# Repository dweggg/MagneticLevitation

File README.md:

# MagneticLevitation
My take on one of those active magnetic levitation projects.

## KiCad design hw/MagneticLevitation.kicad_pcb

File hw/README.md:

# Issues

[ ] -> open
[X] -> found

[X] 1. U1 (3V3 buck) was ordered with JLC PN C61063 (XLSEMI XL1509-5.0E1), which is 5V output, and it should've been C74193 (XLSEMI XL1509-3.3E1). Regardless, it outputs ~4.38V out with ~5.1V in. MCU can be flashed and all aber das ist nicht richtig.

[X] 2. U2 and L2 were removed bc that caused L2 to overheat, something might be wrong with gate drivers (chips or bootstrap). No power for now.

[X] 3. NTC reads 0V, so either pin is bad/misconfigured, or C31 is shorted or something (~0Ohm between TP13 and GND)

[X] 4. Some boards have the inductor rotated 90deg!! That would make the boost not work at all

[X] 5. Vbus sag with pulsed current in a coil around the board. I don't think it's a good idea to have inductors wound in the same axis as the coil we're trying to control, but is there any alternative?

---

Finding: my dumbass didn't configure short circuit rules and there's a group of vias to GND short circuiting the following nets to GND:

- SWA
- SWB
- Gate AH/BH (before gate resistor)
- Vboot_A/B (top side of bootstrap capacitor)
- tempMeas

These are all in the bottom inner layer so it can't be seen on the PCB itself. Fix for now could be a nasty cut traces+magnet wire to destination but that'll require some proper tools... But maybe I'll skip that and probably order again when firmware is ~80% there.

So that explains issues #2 and #3: L2 was overheating bc it's rated at 100mA, and when the boost is disabled, the inductor is getting the 3.3V (well, 4.38V) to the gate driver supply, and since Vboot is shorted to GND, it goes trough R16/R17 to D6/D7 to GND... That's also why the power output (SWA/SWB) was shorted to ground, initially I thought it was some sort of gate driver protection magically turning on the low side switch but no lol.

I think I might have added those two via groups to lower switching loop inductance just before producing outputs and didn't run DRC... That was not a very expensive mistake but a very stupid one for sure. We can use rev1 for improving some other minor things found only after ordering.

---

# Changes to be made
[ ] -> Pending
[S] -> Schematic only
[P] -> Partially done
[X] -> Complete

- [X] 1. Remove violating via groups
- [X] 2. Swap LCSC PN for U1 (XLSEMI XL1509-3.3E1) -> see change #23
- [X] 3. Review LED resistor values: by lowering VCC to the correct 3.3V all LEDs should have a more reasonable brightness, increased to 220R anyways.
- [X] 4. Add external fixed voltage reference, maybe even replacing iRef divider? -> adjusting acq window seems to fix current. Pending tests with real current, but i think it's not needed now that we have a LDO (change #23)
- [X] 5. Add EEPROM?: I don't think we'd need it, and if we really needed it there's a ch32 eeprom emulation using flash, but will give it some thought. So far I don't think we need it, we have plenty of spare flash still with firmware close to 80% of the features, so crossing this one off.
- [X] 6. Review RST button behavior, or think of a way to hw reset the MCU, without firmware -> not necessary, but if needed current design could be made work like that if we flashed with a debugger and not with the bootloader
- [X] 7. Disconnect U2 (MT3608) output without EN pin, PMOS maybe -> not needed, drivers have UVLO at 5.5V
- [X] 8. Remove JLCJLCJLCJLC
- [X] 9. Move power supply section a bit down and leave more clearance with board edge
- [X] 10. Move debug/UART connectors and RST button, also turn them DNP
- [X] 11. Improve bootstrap layout? Works just fine even with the ugly rework, not needed.
- [X] 12. Replace expensive capacitors with something cheaper available as basic JLCPCBA: So far replaced all 22uF with 10uF. Pending proper review with BOM. removed yet another bom line! Was cheap enough already i think.
- [X] 13. Find cuter output connector? Maybe even SMD so back side stays clean -> found a cute but expensive wago. worth it imo
- [X] 14. Review Rgate, since at 12V V_GS, I_G_pk = 12V/10R = 1.2A which is bigger than XJNG2103 1A -> increased to 15R
- [X] 15. Try to reduce electrolytic cap height? If we have XY space we can have half capacitance, half height but x2 parts -> reduced to 5.6mm, same as connector, without decreasing C or increasing diameter. Doesnt make sense to go lower unless connector goes lower, which is not happening
- [X] 16. R16/R17 should be a bit bigger if they need to be hand replaced -> part of bootstrap, same thing, it works
- [X] 17. Testpoints for gates!!! Even if they're difficult to place
- [X] 18. Add revision number in sch and pcb
- [X] 19. Automatic bootloader entry with a MOSFET or similar instead of button (or parallel to button) -> meh not worth it. The flashing experience through bootloader is not that bad. TI is 200x worse even with a fancy jtag probe
- [X] 20. Add potentiometer for setpoint percentage of power
- [X] 21. Add sillkscreen for board ID
- [X] 22. Fix for issue #4 -> added FT Rotation Offset field and set to 0, but investigation is pending. Handled with an assembly remark in prod.
- [X] 23. Fix for issue #5: Replaced 3V3 buck with LDO which removes change #2. I was scared of the inductor saturating and maybe doing something funny with the analog rail. Playing safe even though it clearly works somehow in the current version.

---

# To be verified w current rev before ordering:

[ ] -> Pending
[P] -> Partially done
[X] -> Complete

- [X] 1. Current measurement: At first it looked fine but I noticed it's a little bit asymmetrical with positive and negative setpoints. not a problem, since the important thing is that the controller is fast, not accurate. But maybe can be fine tuned. I think I'm closing it since it doesnt make much of a difference to have 200mA error when the position controller is jerking the current setpoint between -5A and 5A
- [X] 2. Magnetic field measurement: idk lol. It seems proportional to current without magnet (good!), and sort of checks out with what's expected of magnet. Other than that, lol idk. I guess it's fine. the control loop is more important than the accuracy of this sensor
- [X] 3. USB PD + Voltage measurement: ahh I'll have to be smart about how to test this, since my laptop's usb probably can't do very much. we have LEDs tho, that can be useful -> Firmware was able to request 20V from my laptop charger, I think we're good. but having debug + USBPD would be goated. My idea is to have the current comms stack routed to uart and using it instead of the usb port.
- [X] 4. Temperature measurement: cut traces+jump for avoiding issue #3, then thermal cam to verify I guess. So far the measurement seems reasonable with reality, but to be checked against a better measurement. I used a hairdryer to warm the board and i think it's accurate, my cooking skills allow me to distinguish temperatures above and below 60degC so i believe it's fine. its not that critical, even 10deg error would probably be ok. but i think we're at 2deg error, guesstimating. coil gets quite hot too, could we even measure that?
- [P] 5. Gate driver: cut traces+jump (nasty, 6 nets), then program PWM open loop and use scope, verify bootstrap against SPICE -> after i reworked the board i didnt give a fuck and tested power directly without checking gate driver, i have no waveforms but the board is able to control current pretty well. 5W no problem! next up is 100W from USB PD.
- [P] 6. Power: make em MOSFETs warm. Yeah so 5W so far. More to come after USB PD+comms

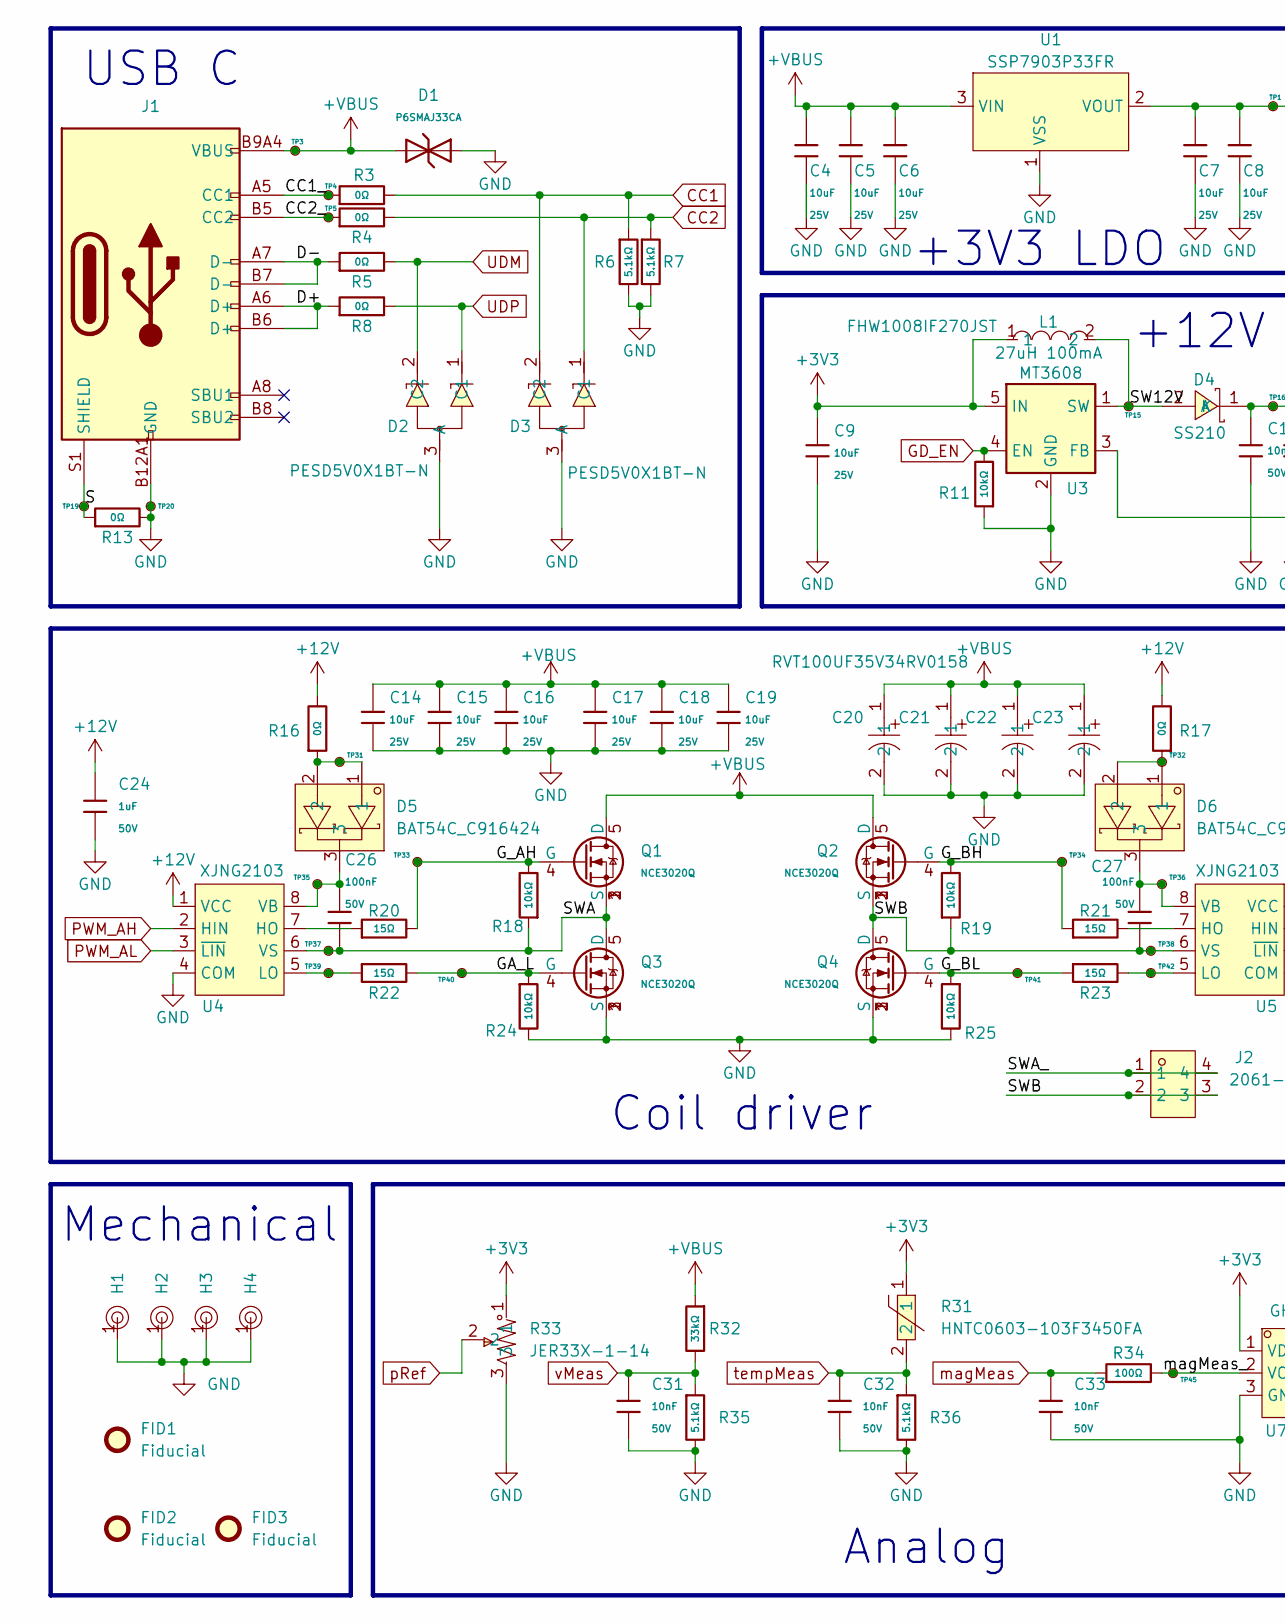
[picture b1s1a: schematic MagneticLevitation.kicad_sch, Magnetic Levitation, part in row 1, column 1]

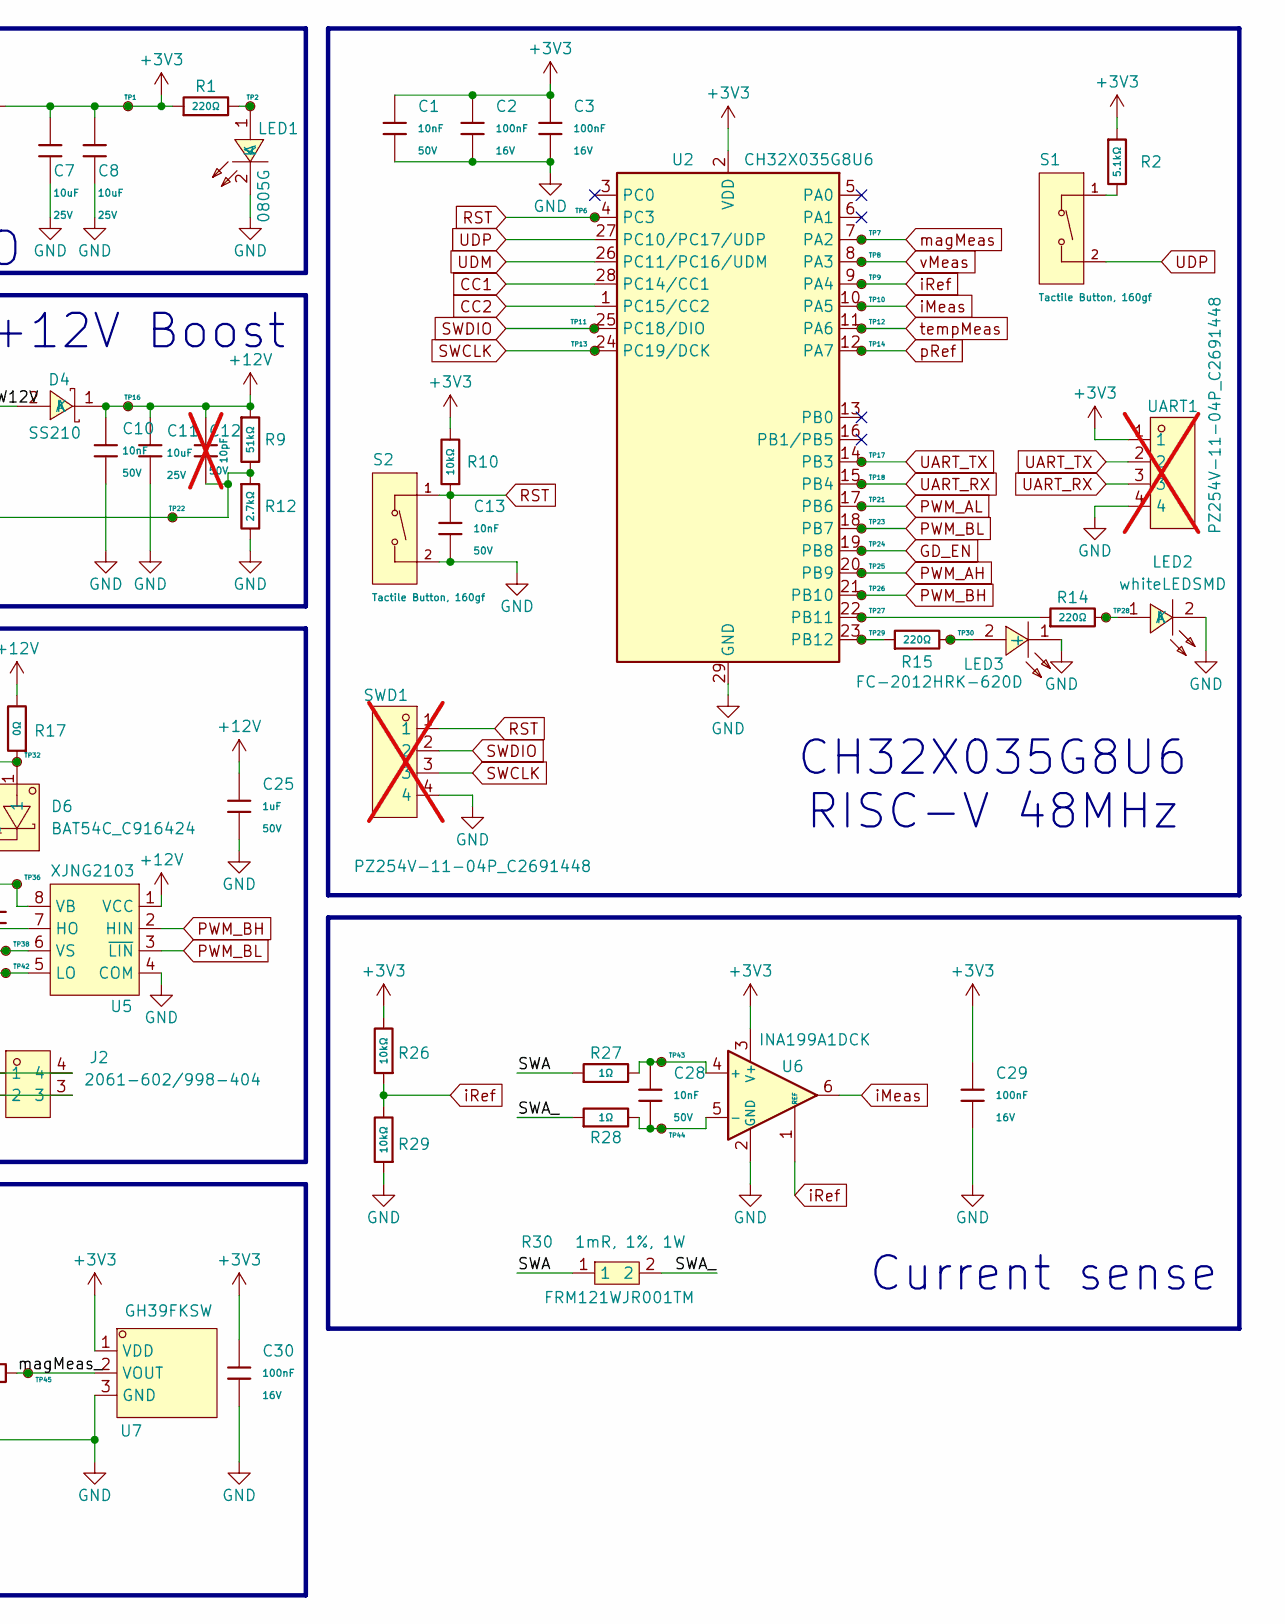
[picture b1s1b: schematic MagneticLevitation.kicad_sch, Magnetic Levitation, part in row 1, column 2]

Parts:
C1, C10, C28: 10nF; C_0402; Voltage Rated 50V; Tolerance ±10%; Part CL05B103KB5NNNC; LCSC C15195
C2, C3, C29, C30: 100nF; C_0402; Voltage Rated 16V; Tolerance ±10%; Part CL05B104KO5NNNC; LCSC C1525
C4, C5, C6, C7, C8, C9, C11, C14, C15, C16, C17, C18, C19: 10uF; C_0805; Voltage Rated 25V; Tolerance ±10%; Part CL21A106KAYNNNE; LCSC C15850
C12: 10pF; C_0603; Voltage Rated 50V; Tolerance ±5%; Part CL10C100JB8NNNC; LCSC C1634; not fitted
C13, C31, C32, C33: 10nF; C_0603; Voltage Rated 50V; Tolerance ±10%; Part 0603B103K500NT; LCSC C57112
C20, C21, C22, C23: RVT100UF35V34RV0158; CAP-SMD_BD6.3-L6.6-W6.6-LS7.2-FD_3; MPN VT100UF35V34RV0158; LCSC Part C2887272
C24, C25: 1uF; C_0805; Voltage Rated 50V; Tolerance ±10%; Part CL21B105KBFNNNE; LCSC C28323
C26, C27: 100nF; C_0603; Voltage Rated 50V; Tolerance ±10%; Part CC0603KRX7R9BB104; LCSC C14663
D1: P6SMAJ33CA; D_DO-214AC(SMA); Breakdown Voltage 36.7V; Part P6SMAJ33CA; LCSC C3019524
D2, D3: PESD5V0X1BT-N; SOT-23-3_L2.9-W1.3-P1.90-LS2.4-BR; MPN PESD5V0X1BT-N; LCSC Part C920303
D4: SS210; SMA_L4.3-W2.6-LS5.2-RD; MPN SS210; LCSC Part C14996
D5, D6: BAT54C_C916424; SOT-23-3_L2.9-W1.3-P1.90-LS2.4-BR; MPN BAT54C; LCSC Part C916424
FID1, FID2, FID3: Fiducial; Fiducial_0.5mm_Mask1.5mm
H1, H2, H3, H4: Hole, 3mm
J1: Connector, USB-TYPE-C-16P; TYPE-C-SMD_HX-TYPE-C-16PIN; LCSC C2927039
J2: 2061-602/998-404; CONN-SMD_2061-602-998-404; MPN 2061-602/998-404; LCSC Part C2765058
L1: 27uH 100mA; IND-SMD_L2.9-W2.8; MPN FHW1008IF270JST; LCSC Part C394070
LED1: 0805G; LED0805-R-RD; MPN KT-0805G; LCSC Part C2297
LED2: whiteLEDSMD; LED0805-R-RD; MPN KT-0805W; LCSC Part C34499
LED3: FC-2012HRK-620D; LED0805-RD; MPN NCD0805R1; LCSC Part C84256
Q1, Q2, Q3, Q4: NCE3020Q; NCE3020Q_DFN3.3x3.3-8L; Part NCE3020Q; LCSC C918240
R1, R14, R15: 220Ω; R_0603; Overload Voltage (Max) 75V; Tolerance ±1%; Part 0603WAF2200T5E; LCSC C22962
R2, R35, R36: 5.1kΩ; R_0603; Overload Voltage (Max) 75V; Tolerance ±1%; Part 0603WAF5101T5E; LCSC C23186
R3, R4, R5, R8, R13, R16, R17: 0Ω; R_0402; Overload Voltage (Max) 50V; Tolerance ±1%; Part 0402WGF0000TCE; LCSC C17168
R6, R7: 5.1kΩ; R_0402; Overload Voltage (Max) 50V; Tolerance ±1%; Part 0402WGF5101TCE; LCSC C25905
R9: 51kΩ; R_0603; Overload Voltage (Max) 75V; Tolerance ±1%; Part 0603WAF5102T5E; LCSC C23196
R10, R11, R18, R19, R24, R25, R26, R29: 10kΩ; R_0402; Overload Voltage (Max) 50V; Tolerance ±1%; Part 0402WGF1002TCE; LCSC C25744
R12: 2.7kΩ; R_0603; Overload Voltage (Max) 75V; Tolerance ±1%; Part 0603WAF2701T5E; LCSC C13167
R20, R21, R22, R23: 15Ω; R_0603; Overload Voltage (Max) 75V; Tolerance ±1%; Part 0603WAF150JT5E; LCSC C22810
R27, R28: 1Ω; R_0603; Overload Voltage (Max) 75V; Tolerance ±1%; Part 0603WAF100KT5E; LCSC C22936
R30: 1mR, 1%, 1W; R1206; MPN FRM121WJR001TM; LCSC Part C7419993
R31: HNTC0603-103F3450FA; R0603; MPN HNTC0603-103F3450FA; LCSC Part C49247665
R32: 33kΩ; R_0603; Overload Voltage (Max) 75V; Tolerance ±1%; Part 0603WAF3302T5E; LCSC C4216
R33: JER33X-1-14; RES-ADJ-SMD_JER33X-1-14; MPN JER33X-1-14; LCSC Part C48997896
R34: 100Ω; R_0603; Overload Voltage (Max) 75V; Tolerance ±1%; Part 0603WAF1000T5E; LCSC C22775
S1, S2: Tactile Button, 160gf; SW_TS-1088-AR02016; Voltage Rating (Dc) 12V; Part TS-1088-AR02016; LCSC C720477
SWD1: PZ254V-11-04P_C2691448; HDR-TH_4P-P2.54-V-M; MPN PZ254V-11-04P; LCSC Part C2691448; not fitted
TP1, TP2, TP3, TP4, TP5, TP6, TP7, TP8, TP9, TP10, TP11, TP12, TP13, TP14, TP15, TP16, TP17, TP18, TP19, TP20, TP21, TP22, TP23, TP24, TP25, TP26, TP27, TP28, TP29, TP30, TP31, TP32, TP33, TP34, TP35, TP36, TP37, TP38, TP39, TP40, TP41, TP42, TP43, TP44, TP45: TestPoint_Small; TestPoint_Pad_D1.0mm
U1: SSP7903P33FR; SOT-223-3_L6.5-W3.4-P2.30-LS7.0-BR-1; MPN SSP7903P33FR; LCSC Part C5199839
U2: CH32X035G8U6; WQFN-28-1EP_4x4mm_P0.4mm_EP2.7x2.7mm; LCSC C7437027
U3: MT3608; SOT-23-6; LCSC C84817
U4, U5: XJNG2103; SOIC-8_L5.0-W4.0-P1.27-LS6.0-BL; LCSC C2887735
U6: INA199A1DCK; SOT-363_SC-70-6; LCSC C59135
U7: GH39FKSW; SOT-23-3_L2.9-W1.3-P1.90-LS2.4-BR; MPN GH39FKSW; LCSC Part C266230
UART1: PZ254V-11-04P_C2691448; HDR-TH_4P-P2.54-V-M; MPN PZ254V-11-04P; LCSC Part C2691448; not fitted

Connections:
+3V3: C1.1, C2.1, C3.1, C7.1, C8.1, C9.1, C29.1, C30.1, L1.1, R1.1, R2.1, R10.2, R26.2, R31.1, R33.1, TP1.1 (1_1), U1.2 (VOUT), U2.2 (VDD), U3.5 (IN), U6.3 (V+), U7.1 (VDD), UART1.1
+12V: C10.1, C11.1, C12.1, C24.1, C25.1, D4.1 (K), R9.1, R16.2, R17.2, TP16.1 (1_1), U4.1 (VCC), U5.1 (VCC)
+VBUS: C4.1, C5.1, C6.1, C14.1, C15.1, C16.1, C17.1, C18.1, C19.1, C20.1, C21.1, C22.1, C23.1, D1.1, J1.A9B4 (VBUS), J1.B9A4 (VBUS), Q1.5 (D), Q2.5 (D), R32.1, TP3.1 (1_1), U1.3 (VIN)
/CC1_: J1.A5 (CC1), R3.1, TP4.1 (1_1)
/CC2_: J1.B5 (CC2), R4.1, TP5.1 (1_1)
/D+: J1.A6 (D+), J1.B6 (D+), R8.1
/D-: J1.A7 (D-), J1.B7 (D-), R5.1
/GA_L: Q3.4 (G), R22.2, R24.1, TP40.1 (1_1)
/G_AH: Q1.4 (G), R18.2, R20.2, TP33.1 (1_1)
/G_BH: Q2.4 (G), R19.2, R21.1, TP34.1 (1_1)
/G_BL: Q4.4 (G), R23.1, R25.1, TP41.1 (1_1)
/S: J1.S1 (SHIELD), R13.1, TP19.1 (1_1)
/SW12V: D4.2 (A), L1.2, TP15.1 (1_1), U3.1 (SW)
/SWA: C26.2, Q1.1 (S), Q1.2 (S), Q1.3 (S), Q3.5 (D), R18.1, R27.1, R30.1, TP37.1 (1_1), U4.6 (VS)
/SWA_: J2.1, J2.4, R28.1, R30.2
/SWB: C27.2, J2.2, J2.3, Q2.1 (S), Q2.2 (S), Q2.3 (S), Q4.5 (D), R19.1, TP38.1 (1_1), U5.6 (VS)
/magMeas_: R34.2, TP45.1 (1_1), U7.2 (VOUT)
CC1: D3.2 (C2), R3.2, R6.1, U2.28 (PC14/CC1)
CC2: D3.1 (C1), R4.2, R7.1, U2.1 (PC15/CC2)
GD_EN: R11.2, TP24.1 (1_1), U2.19 (PB8), U3.4 (EN)
GND: C1.2, C2.2, C3.2, C4.2, C5.2, C6.2, C7.2, C8.2, C9.2, C10.2, C11.2, C13.2, C14.2, C15.2, C16.2, C17.2, C18.2, C19.2, C20.2, C21.2, C22.2, C23.2, C24.2, C25.2, C29.2, C30.2, C31.2, C32.2, C33.2, D1.2, D2.3 (A), D3.3 (A), H1.1, H2.1, H3.1, H4.1, J1.A12B1 (GND), J1.B12A1 (GND), LED1.2 (K), LED2.2 (K), LED3.1 (-), Q3.1 (S), Q3.2 (S), Q3.3 (S), Q4.1 (S), Q4.2 (S), Q4.3 (S), R6.2, R7.2, R11.1, R12.2, R13.2, R24.2, R25.2, R29.1, R33.3, R35.2, R36.2, S2.2 (B), SWD1.4, TP20.1 (1_1), U1.1 (VSS), U2.29 (GND), U3.2 (GND), U4.4 (COM), U5.4 (COM), U6.2 (GND), U7.3 (GND), UART1.4
unnamed: D5.1, D5.2, R16.1, TP31.1 (1_1)
unnamed: D6.1, D6.2, R17.1, TP32.1 (1_1)
unnamed: LED1.1 (A), R1.2, TP2.1 (1_1)
unnamed: LED2.1 (A), R14.2, TP28.1 (1_1)
unnamed: LED3.2 (+), R15.2, TP30.1 (1_1)
unnamed: R2.2, S1.1 (A)
unnamed: R14.1, TP27.1 (1_1), U2.22 (PB11)
unnamed: R15.1, TP29.1 (1_1), U2.23 (PB12)
unnamed: C12.2, R9.2, R12.1, TP22.1 (1_1), U3.3 (FB)
unnamed: R20.1, U4.7 (HO)
unnamed: R22.1, TP39.1 (1_1), U4.5 (LO)
unnamed: C26.1, D5.3, TP35.1 (1_1), U4.8 (VB)
unnamed: R21.2, U5.7 (HO)
unnamed: R23.2, TP42.1 (1_1), U5.5 (LO)
unnamed: C27.1, D6.3, TP36.1 (1_1), U5.8 (VB)
unnamed: C28.1, R27.2, TP43.1 (1_1), U6.4 (+)
unnamed: C28.2, R28.2, TP44.1 (1_1), U6.5 (-)
PWM_AH: TP25.1 (1_1), U2.20 (PB9), U4.2 (HIN)
PWM_AL: TP21.1 (1_1), U2.17 (PB6), U4.3 (~LIN)
PWM_BH: TP26.1 (1_1), U2.21 (PB10), U5.2 (HIN)
PWM_BL: TP23.1 (1_1), U2.18 (PB7), U5.3 (~LIN)
RST: C13.1, R10.1, S2.1 (A), SWD1.1, TP6.1 (1_1), U2.4 (PC3)
SWCLK: SWD1.3, TP13.1 (1_1), U2.24 (PC19/DCK)
SWDIO: SWD1.2, TP11.1 (1_1), U2.25 (PC18/DIO)
UART_RX: TP18.1 (1_1), U2.15 (PB4), UART1.3
UART_TX: TP17.1 (1_1), U2.14 (PB3), UART1.2
UDM: D2.2 (C2), R5.2, U2.26 (PC11/PC16/UDM)
UDP: D2.1 (C1), R8.2, S1.2 (B), U2.27 (PC10/PC17/UDP)
iMeas: TP10.1 (1_1), U2.10 (PA5), U6.6
iRef: R26.1, R29.2, TP9.1 (1_1), U2.9 (PA4), U6.1 (REF)
magMeas: C33.1, R34.1, TP7.1 (1_1), U2.7 (PA2)
pRef: R33.2, TP14.1 (1_1), U2.12 (PA7)
tempMeas: C32.1, R31.2, R36.1, TP12.1 (1_1), U2.11 (PA6)
vMeas: C31.1, R32.2, R35.1, TP8.1 (1_1), U2.8 (PA3)

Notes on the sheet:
+3V3 LDO
Current sense
CH32X035G8U6 RISC-V 48MHz
Coil driver
Mechanical
Analog
+12V Boost
USB C

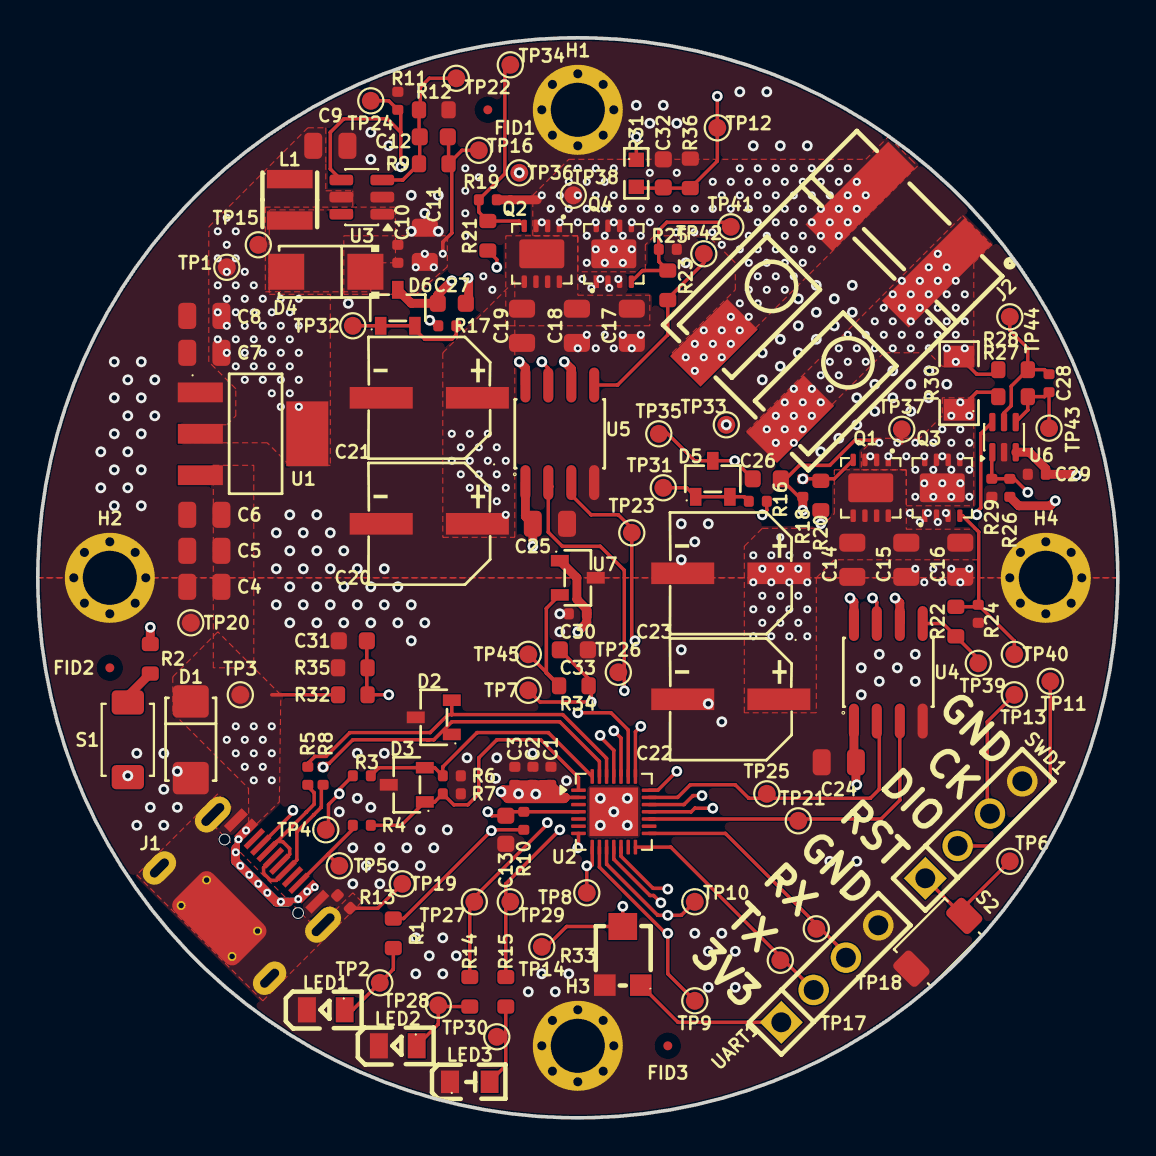
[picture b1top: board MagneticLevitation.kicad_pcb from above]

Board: 4 copper layers, 60.0 x 60.0 mm, 148 parts (0 on the bottom side), 55 nets.

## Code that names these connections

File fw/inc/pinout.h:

#ifndef PINOUT_H
#define PINOUT_H

/*
 * Board pin definitions
 * MCU: CH32X035G8U6
 */


/*
 * Analog measurements
 */
#define PIN_MAG_MEAS       PA2     // magMeas
#define PIN_V_MEAS         PA3     // vMeas
#define PIN_I_REF          PA4     // iRef
#define PIN_I_MEAS         PA5     // iMeas
#define PIN_TEMP_MEAS      PA6     // tempMeas


/*
 * USB
 *
 * CH32X035 USB pins:
 * UDP = USB D+
 * UDM = USB D-
 */
#define PIN_USB_DP         PC10    // UDP
#define PIN_USB_DM         PC11    // UDM


/*
 * UART
 */
#define PIN_UART_TX        PB3
#define PIN_UART_RX        PB4


/*
 * PWM outputs
 */
#define PIN_PWM_AL         PB6
#define PIN_PWM_BL         PB7
#define PIN_PWM_AH         PB9
#define PIN_PWM_BH         PB10
#define PIN_GD_EN          PB8


/*
 * LEDs
 */
#define PIN_LED_WHITE      PB11
#define PIN_LED_RED        PB12


/*
 * User buttons
 */
#define PIN_RST_BUTTON     PC3     // RST button

/*
 * Programming / debugging
 */
#define PIN_SWDIO          PC18
#define PIN_SWCLK          PC19

#endif // PINOUT_H
